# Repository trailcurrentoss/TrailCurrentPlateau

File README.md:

# TrailCurrent Plateau

Vehicle leveling module that monitors trailer tilt angles and computes per-corner height adjustments via a CAN bus interface with OTA firmware update capability. Part of the [TrailCurrent](https://trailcurrent.com) open-source vehicle platform.

## Hardware Overview

- **Microcontroller:** ESP32-S3 ([Waveshare ESP32-S3-RS485-CAN](https://www.waveshare.com/esp32-s3-rs485-can.htm))
- **IMU:** [DFRobot SEN0253](https://wiki.dfrobot.com/sen0253/) Gravity 10-DOF AHRS (Bosch BNO055)
- **Function:** Vehicle leveling with CAN bus communication
- **Key Features:**
  - BNO055 IMU for pitch/roll measurement with auto-calibration
  - Per-corner height adjustment calculation from vehicle dimensions
  - Three mounting orientations (floor, left wall, right wall) with axis remapping
  - CAN bus communication at 500 kbps
  - Vehicle configuration (dimensions, mounting) received via CAN and stored in NVS
  - Over-the-air (OTA) firmware updates via WiFi (credentials provisioned via CAN)
  - mDNS-based device discovery for Headwaters integration
  - Custom flash partition layout with dual OTA slots

## Hardware Requirements

Plateau is built entirely from off-the-shelf modules wired together — there is no custom PCB.

### Bill of Materials

| Qty | Part | Notes |
|-----|------|-------|
| 1 | [Waveshare ESP32-S3-RS485-CAN](https://www.waveshare.com/esp32-s3-rs485-can.htm) | ESP32-S3R8 (8MB PSRAM, 16MB flash), built-in isolated CAN transceiver (TJA1051), built-in isolated RS485 transceiver (unused), 7-36V DC input or 5V USB-C — runs directly from the vehicle 12V supply |
| 1 | [DFRobot SEN0253](https://wiki.dfrobot.com/sen0253/) Gravity 10-DOF AHRS | Bosch BNO055 IMU (I2C 0x28) + BMP280 (unused). Ships with a Gravity 4-pin I2C cable |
| 1 | 20-pin IDC 2x10 ribbon cable | Connects to the board's user header; only wires 1, 3, 13 and 15 are used |
| 1 | Enclosure | FreeCAD design in [`CAD/`](CAD/) |

### Pin Connections

| IDC Pin | GPIO | Function |
|---------|------|----------|
| 1 | — | 3.3V → IMU VCC |
| 3 | — | GND → IMU GND |
| 13 | 5 | I2C SDA (BNO055) |
| 15 | 6 | I2C SCL (BNO055) |
| — | 15 | CAN TX (onboard transceiver) |
| — | 16 | CAN RX (onboard transceiver) |

CAN H / CAN L and 7-36V power land on the board's screw terminals, not the ribbon cable. See [DOCS/plateau-ribbon-cable.png](DOCS/plateau-ribbon-cable.png) for the full wiring reference.

## Firmware

ESP-IDF native firmware in the `main/` directory.

**Prerequisites:**
- [ESP-IDF](https://docs.espressif.com/projects/esp-idf/en/latest/esp32s3/get-started/) v5.2 or later

**Build and flash:**
```bash
# Set ESP-IDF target
idf.py set-target esp32s3

# Build firmware
idf.py build

# Upload to board (serial)
idf.py flash

# Monitor serial output
idf.py monitor

# Build, flash, and monitor in one command
idf.py build flash monitor
```

**Release build (`build-all.sh`):**

```bash
./build-all.sh
```

Produces both release binaries:

| File | Use |
|------|-----|
| `build/plateau.bin` | App-only image — OTA via Headwaters or `curl` |
| `build/plateau_merged.bin` | Bootloader + partition table + OTA data + app — web flasher, or direct flash at `0x0` |

Never use the merged binary for OTA: it starts with the bootloader, not an app header, and fails `esp_ota_end` validation.

**Direct flash of the merged binary:**
```bash
esptool.py --chip esp32s3 write_flash 0x0 build/plateau_merged.bin
```

**OTA update (after initial flash):**
```bash
curl -X POST http://esp32-XXYYZZ.local/ota --data-binary @build/plateau.bin
```

### Flash Layout

16MB flash, DIO mode, dual OTA slots (`partitions.csv`):

| Partition | Offset | Size |
|-----------|--------|------|
| nvs | 0x9000 | 20KB |
| otadata | 0xE000 | 8KB |
| app0 (ota_0) | 0x10000 | 5.9MB |
| app1 (ota_1) | 0x600000 | 5.9MB |
| spiffs | 0xBF0000 | 4.1MB |

### Firmware Architecture

The firmware uses FreeRTOS tasks for concurrent operation:

| Task | Priority | Stack | Function |
|------|----------|-------|----------|
| twai | 5 | 4096 | CAN bus RX/TX, leveling computation, IMU reads |
| ota | 3 | 8192 | OTA update (spawned on demand, non-blocking) |
| discovery | 3 | 8192 | mDNS discovery (spawned on demand, non-blocking) |

OTA and discovery run as separate tasks to avoid blocking CAN bus communication. Mutual exclusion prevents both from running simultaneously.

### Source Files

| File | Purpose |
|------|---------|
| `main.c` | Application entry, TWAI task, leveling logic, CAN protocol |
| `bno055.c/h` | BNO055 IMU driver for the DFRobot SEN0253 (ESP-IDF I2C master, 100 kHz) |
| `wifi_config.c/h` | WiFi credentials, connect/disconnect, CAN provisioning |
| `ota.c/h` | Task-based OTA with HTTP server and mDNS |
| `discovery.c/h` | Task-based mDNS discovery for Headwaters |

### CAN Bus Protocol

- **Receive ID `0x00`:** OTA update trigger — initiates firmware update when device MAC matches
- **Receive ID `0x01`:** WiFi credential provisioning — multi-frame protocol to store SSID/password in NVS
- **Receive ID `0x02`:** Discovery trigger — joins WiFi, advertises via mDNS, waits for Headwaters confirmation
- **Transmit ID `0x04`:** Firmware version report — sent once on boot: `[mac3, mac4, mac5, major, minor, patch]`
- **Receive ID `0x36`:** Leveling configuration — set mounting surface, vehicle length/width, persist to NVS
- **Transmit ID `0x37`:** Tilt data — pitch/roll angles (×100) and front-back/left-right height diffs in mm
- **Transmit ID `0x38`:** Corner data — per-corner height adjustments in mm (normalized, lowest = 0)
- **Transmit ID `0x39`:** Status data — IMU connection, calibration levels, mounting orientation
- *(Plateau CAN IDs were reallocated 2026-05-19 from the original 0x20/0x30/0x31/0x32 block to the contiguous 0x36-0x39 block when Borealis claimed 0x20 for its safety frame.)*
- CAN speed: 500 kbps

### WiFi Credentials

WiFi credentials are provisioned over the CAN bus (ID `0x01`) and stored in NVS. No hardcoded credentials or secrets files needed.

## Project Structure

```
├── EDA/                          # Archived KiCAD design from an earlier custom-PCB revision (no longer used)
├── CAD/                          # FreeCAD enclosure design
├── main/                         # ESP-IDF firmware source
│   ├── main.c                    # Application entry, TWAI task, leveling logic
│   ├── bno055.c/h                # BNO055 IMU I2C driver
│   ├── wifi_config.c/h           # WiFi credentials and CAN provisioning
│   ├── ota.c/h                   # OTA firmware update (task-based)
│   ├── discovery.c/h             # mDNS device discovery (task-based)
│   ├── CMakeLists.txt            # Component build configuration
│   └── idf_component.yml         # ESP-IDF component dependencies
├── CMakeLists.txt                # Root ESP-IDF project file
├── DOCS/                         # Ribbon cable wiring diagram (SVG source + PNG)
├── build-all.sh                  # Release build: OTA + merged (web flasher) binaries
├── sdkconfig.defaults            # ESP-IDF build defaults
├── partitions.csv                # 16MB flash partition layout (dual OTA)
├── LICENSE                       # MIT License
└── README.md                     # This file
```

## License

MIT License - See LICENSE file for details.

You are free to use, modify, and distribute these designs for personal or commercial purposes.

## Contributing

Improvements and contributions are welcome! Please submit issues or pull requests.

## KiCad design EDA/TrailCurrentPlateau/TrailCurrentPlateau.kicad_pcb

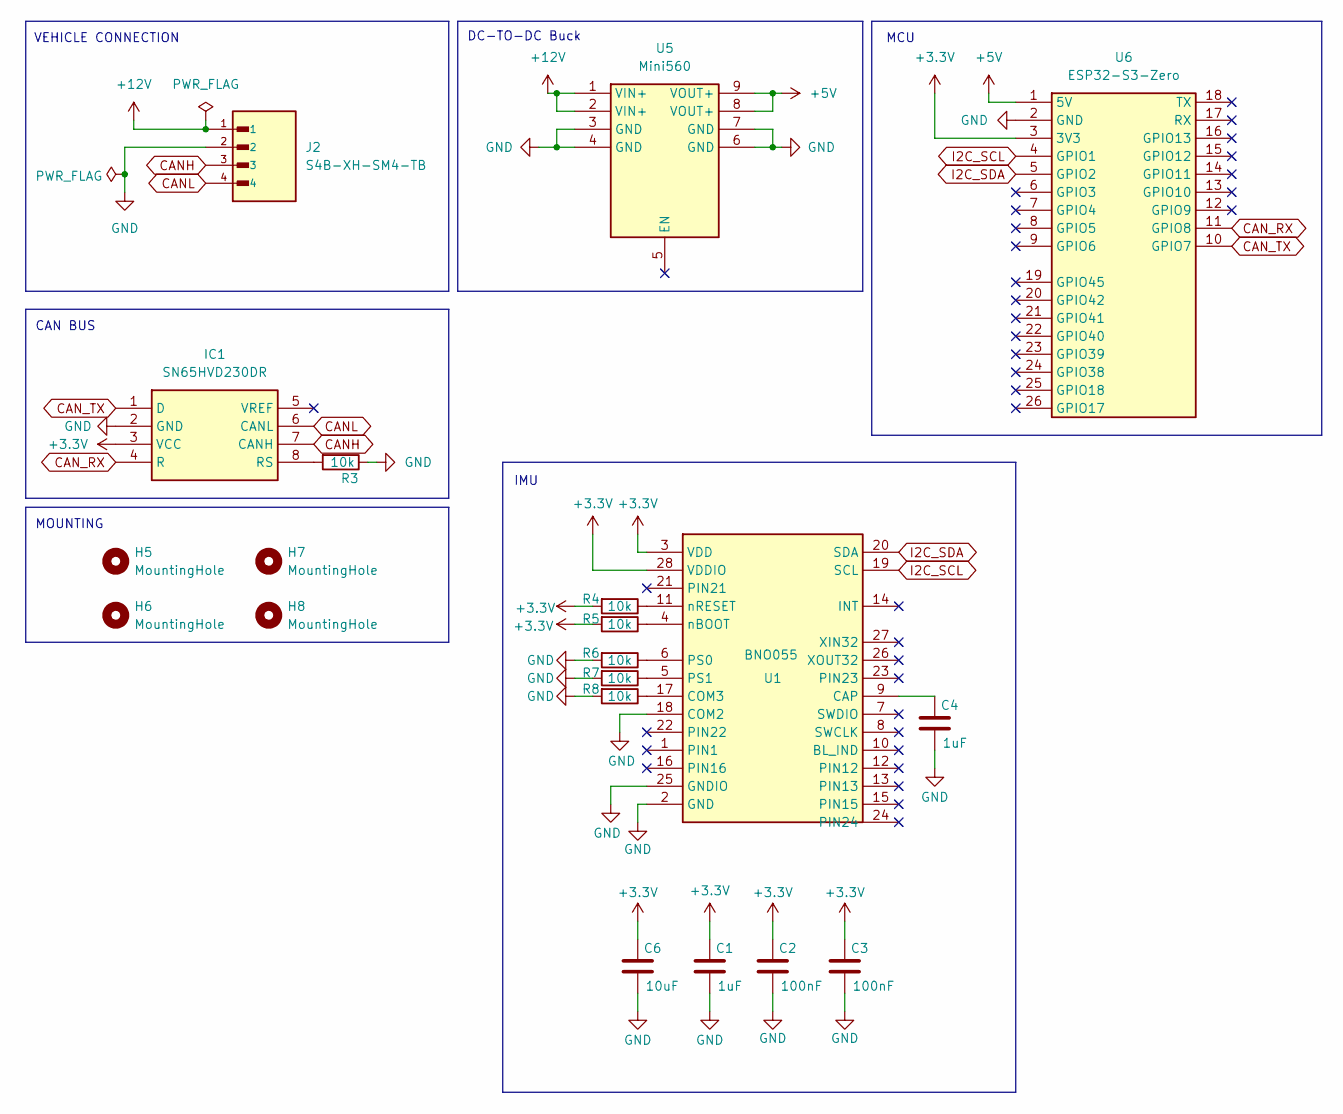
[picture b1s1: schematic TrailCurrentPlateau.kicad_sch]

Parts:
C1, C4: 1uF; C_1206_3216Metric
C2, C3: 100nF; C_1206_3216Metric
C6: 10uF; C_1206_3216Metric
H5, H6, H7, H8: MountingHole; MountingHole_2.5mm
IC1: SN65HVD230DR; Mouser Part Number 595-SN65HVD230DR
J2: S4B-XH-SM4-TB; JST_S4B-XH-SM4-TB; LCSC Part C161861
R3, R4, R5, R6, R7, R8: 10k; R_1206_3216Metric_Pad1.30x1.75mm_HandSolder
U1: BNO055; BNO055_LGA-28_3.8x5.2mm
U5: Mini560; Manufacturer_Part_Number Mini560
U6: ESP32-S3-Zero; ESP32-S3-Zero_TH; Manufacturer_Part_Number ESP32-S3-Zero

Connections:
+3.3V: C1.1, C2.1, C3.1, C6.1, IC1.3 (VCC), R4.2, R5.2, U1.3 (VDD), U1.28 (VDDIO), U6.3 (3V3)
+5V: U5.8 (VOUT+), U5.9 (VOUT+), U6.1 (5V)
+12V: J2.1, U5.1 (VIN+), U5.2 (VIN+)
CANH: IC1.7 (CANH), J2.3
CANL: IC1.6 (CANL), J2.4
CAN_RX: IC1.4 (R), U6.11 (GPIO8)
CAN_TX: IC1.1 (D), U6.10 (GPIO7)
GND: C1.2, C2.2, C3.2, C4.2, C6.2, IC1.2 (GND), J2.2, R3.1, R6.2, R7.2, R8.2, U1.2 (GND), U1.18 (COM2), U1.25 (GNDIO), U5.3 (GND), U5.4 (GND), U5.6 (GND), U5.7 (GND), U6.2 (GND)
I2C_SCL: U1.19 (SCL), U6.4 (GPIO1)
I2C_SDA: U1.20 (SDA), U6.5 (GPIO2)
unnamed: IC1.8 (RS), R3.2
unnamed: C4.1, U1.9 (CAP)
unnamed: R8.1, U1.17 (COM3)
unnamed: R6.1, U1.6 (PS0)
unnamed: R7.1, U1.5 (PS1)
unnamed: R5.1, U1.4 (nBOOT)
unnamed: R4.1, U1.11 (nRESET)

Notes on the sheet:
IMU
DC-TO-DC Buck
MCU
VEHICLE CONNECTION
MOUNTING
CAN BUS

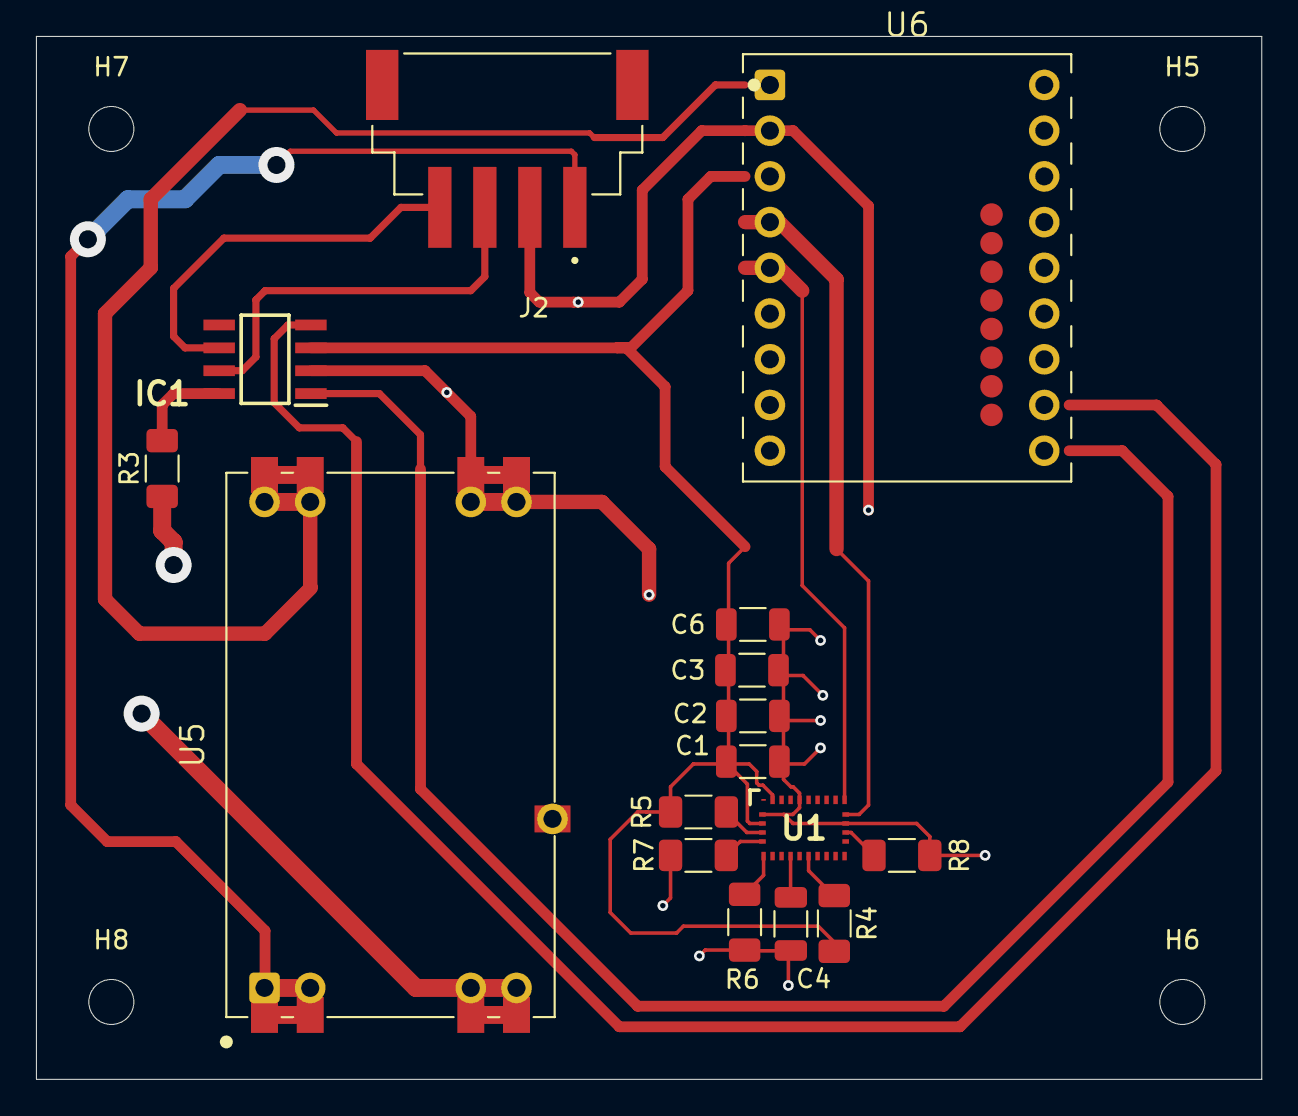
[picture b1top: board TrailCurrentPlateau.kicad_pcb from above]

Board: 2 copper layers, 68.1 x 57.9 mm, 20 parts (0 on the bottom side), 17 nets.

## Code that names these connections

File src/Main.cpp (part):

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#include "Globals.h"

// --- Pin definitions ---
#define I2C_SDA 1
#define I2C_SCL 2
#define CAN_TX GPIO_NUM_7
#define CAN_RX GPIO_NUM_8
#define RGB_LED_PIN 21

void setLed(uint8_t r, uint8_t g, uint8_t b) {
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
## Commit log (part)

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2026-03-15 Moved to ESP32S3 Zero board, adafruit bno055 and standard approach for CAN Bus and OTA
2026-03-15 Initial working state
2026-03-15 DIY EDA ready, CAM milling oeprations added
2026-03-16 EDA Changes to fix Adafruit BNO055 older style footprint
2026-03-17 Updated toolpaths with revised BNO055 footprint
2026-03-22 Updates to improve the calibration process and communicate that to headwaters.
2026-03-28 Moved to ESP-IDF
2026-03-28 Fixing issue with CAN Bus stops responding when discovery happens
2026-03-29 Changes to provide version on OTA
2026-04-12 Adding discovery for this device
